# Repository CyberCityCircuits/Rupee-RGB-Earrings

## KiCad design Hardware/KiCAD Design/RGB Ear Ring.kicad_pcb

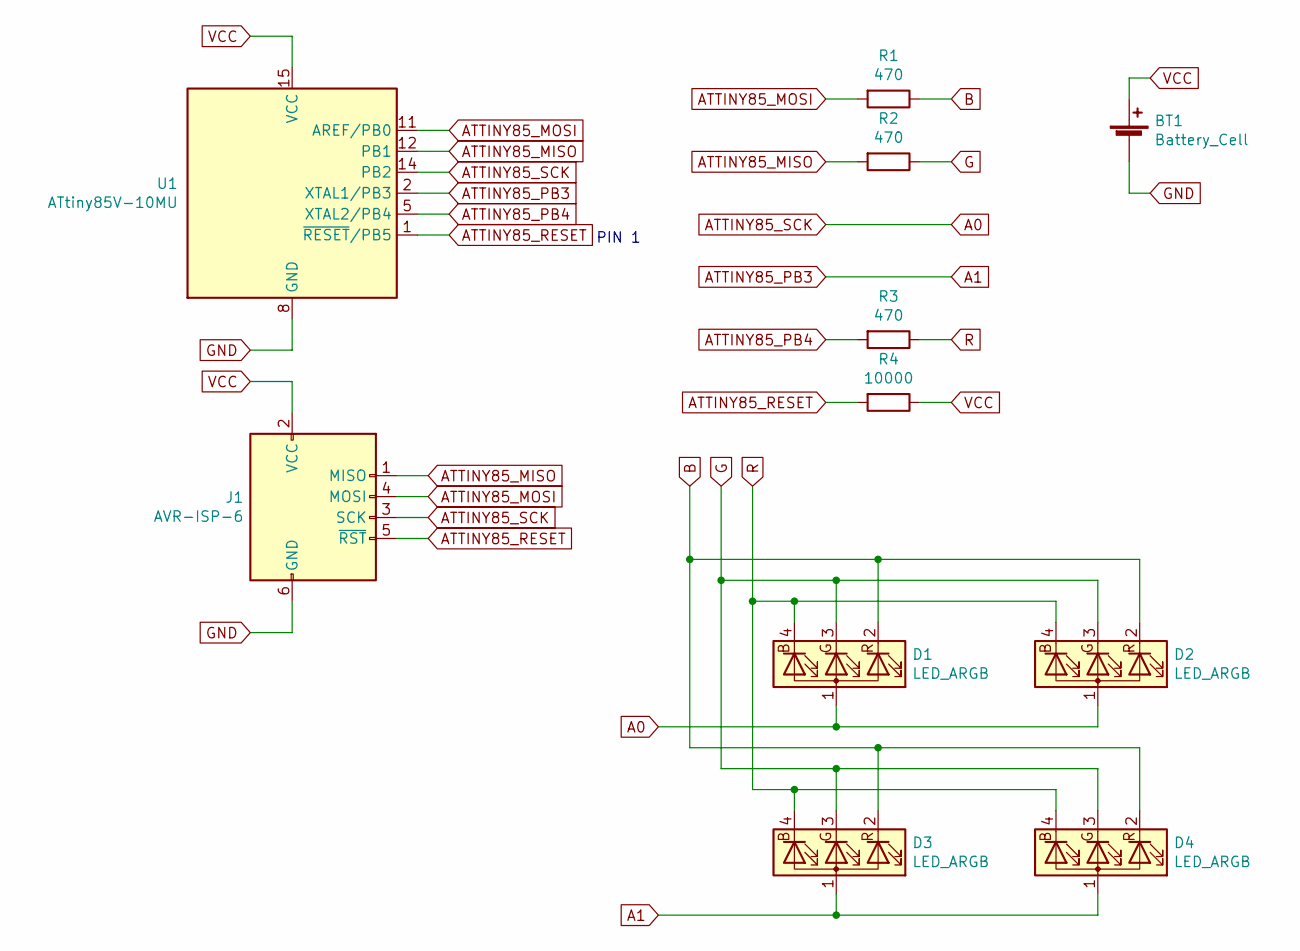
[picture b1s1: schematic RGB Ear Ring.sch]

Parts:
BT1: Battery_Cell; Schematic - Battery CR2032
D1, D2, D3, D4: LED_ARGB; LED_Cree-PLCC4_2x2mm_CW
J1: AVR-ISP-6; PinSocket_2x03_P2.54mm_Vertical
R1, R2, R3: 470; R_0603
R4: 10000; R_0603
U1: ATtiny85V-10MU; QFN-20-1EP_4x4mm_P0.5mm_EP2.6x2.6mm

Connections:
A0: D1.1 (A), D2.1 (A), J1.3 (SCK), U1.14 (PB2)
A1: D3.1 (A), D4.1 (A), U1.2 (XTAL1/PB3)
ATTINY85_MISO: J1.1 (MISO), R2.2, U1.12 (PB1)
ATTINY85_MOSI: J1.4 (MOSI), R1.2, U1.11 (AREF/PB0)
ATTINY85_PB4: R3.2, U1.5 (XTAL2/PB4)
ATTINY85_RESET: J1.5 (~RST), R4.2, U1.1 (~RESET~/PB5)
B: D1.2 (RK), D2.2 (RK), D3.2 (RK), D4.2 (RK), R1.1
G: D1.3 (GK), D2.3 (GK), D3.3 (GK), D4.3 (GK), R2.1
GND: BT1.2 (-), J1.6 (GND), U1.8 (GND), U1.21 (GND)
R: D1.4 (BK), D2.4 (BK), D3.4 (BK), D4.4 (BK), R3.1
VCC: BT1.1 (+), J1.2 (VCC), R4.1, U1.15 (VCC)

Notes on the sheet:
PIN 1

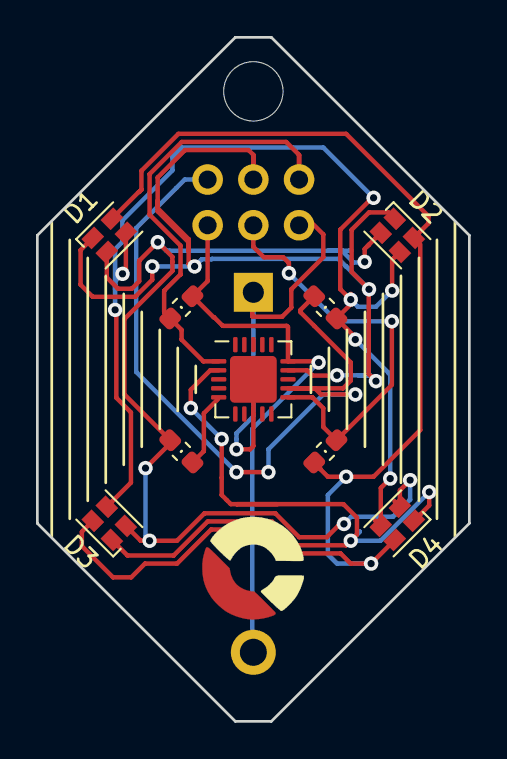
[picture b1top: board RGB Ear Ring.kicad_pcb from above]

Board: 2 copper layers, 24.0 x 38.0 mm, 12 parts (1 on the bottom side), 11 nets.

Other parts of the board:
 : 3mm_Hole; 3mm Mount Hole

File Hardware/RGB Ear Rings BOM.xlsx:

Designator | Item | Description | Footprint | Manufacturer | Part Number | Vendor | Vendor PN |  | Unit Cost
U1 | MCU | ATTING85V-15MT |  | Microchip | ATTINY85V-15MT | DigiKey | 1611-ATTINY85V-15MTCT-ND |  | 0.58799999999999997 | 0.5
D1 | RGB LED |  | PLCC4 | Broadcom | ASMB-KTF0-0A306 | Mouser | 630-ASMB-KTF0-0A306 |  | 0.20699999999999999 | 0.4
D2 | RGB LED |  | PLCC4 | Broadcom | ASMB-KTF0-0A306 | Mouser | 630-ASMB-KTF0-0A306 |  | 0.20699999999999999 | 0.4
D3 | RGB LED |  | PLCC4 | Broadcom | ASMB-KTF0-0A306 | Mouser | 630-ASMB-KTF0-0A306 |  | 0.20699999999999999 | 0.4
D4 | RGB LED |  | PLCC4 | Broadcom | ASMB-KTF0-0A306 | Mouser | 630-ASMB-KTF0-0A306 |  | 0.20699999999999999 | 0.4
R1 | Resistor 0603 | 470 Ohm | 0603
R2 | Resistor 0603 | 470 Ohm | 0603
R3 | Resistor 0603 | 470 Ohm | 0603
R4 | Resistor 0603 | 10K Ohm | 0603
BT1 | Battery Holder
 | Battery
 | Earring Hooks

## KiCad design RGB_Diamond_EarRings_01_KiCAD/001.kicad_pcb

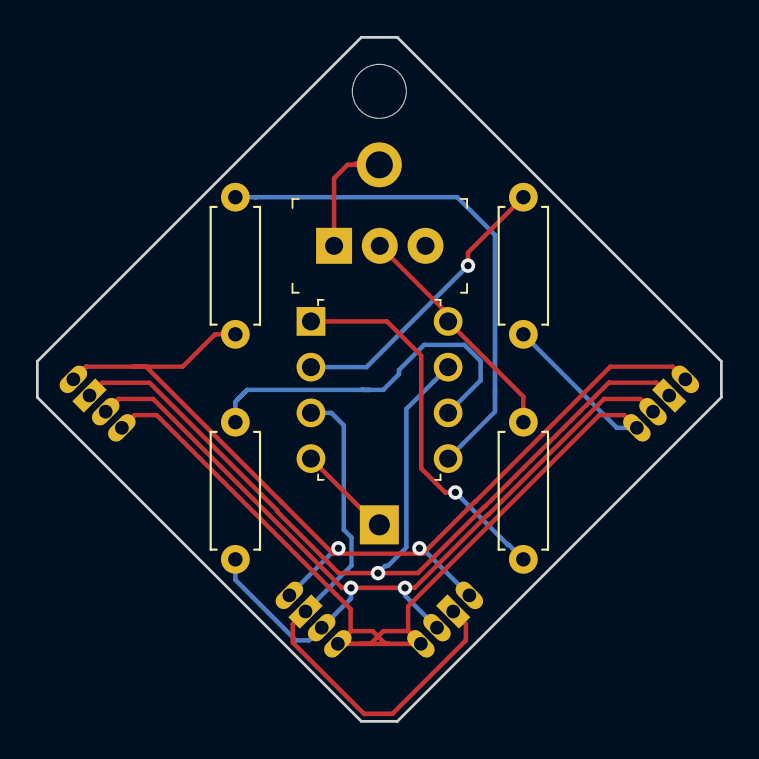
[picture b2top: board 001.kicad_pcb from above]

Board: 2 copper layers, 38.0 x 38.0 mm, 11 parts (1 on the bottom side), 12 nets.

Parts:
BT1: Battery_Cell; Battery_Holder_Coin_2032_BS-7
D1, D2, D3, D4: LED_RAGB; DREAM_RGB_0.9mm_Hole
R1, R2, R3: 470; R_Axial_DIN0207_L6.3mm_D2.5mm_P7.62mm_Horizontal
R4: 10000; R_Axial_DIN0207_L6.3mm_D2.5mm_P7.62mm_Horizontal
SW1: SW_SPDT; Switch_Toggle_ATE1D-2M3-10-Z
U1: ATTINY85-20PU; DIP-8_W7.62mm

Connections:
A0: D1.2, D2.2, U1.7
A1: D3.2, D4.2, U1.3
B: D1.4, D2.4, D3.4, D4.4, R3.1
BATT: BT1.Pos, SW1.1
G: D1.3, D2.3, D3.3, D4.3, R2.1
GND: BT1.Neg, U1.4
PB0: R1.2, U1.5
PB1: R2.2, U1.6
PB3: R3.2, U1.2
PB5: R4.2, U1.1
R: D1.1, D2.1, D3.1, D4.1, R1.1
VCC: R4.1, SW1.2, U1.8

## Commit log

2019-03-05 Added KiCAD files.
    Added KiCAD files.
2020-08-03 Initial Upload for Rupee Design (1040)
2020-10-02 Updated With All of the Deisgn Files
2020-10-08 Posted 1051 - (V2.1)
    Hardware Update for newer version. Allows for PWM function on Blue pins.
2020-11-03 Software for 1051 Version
